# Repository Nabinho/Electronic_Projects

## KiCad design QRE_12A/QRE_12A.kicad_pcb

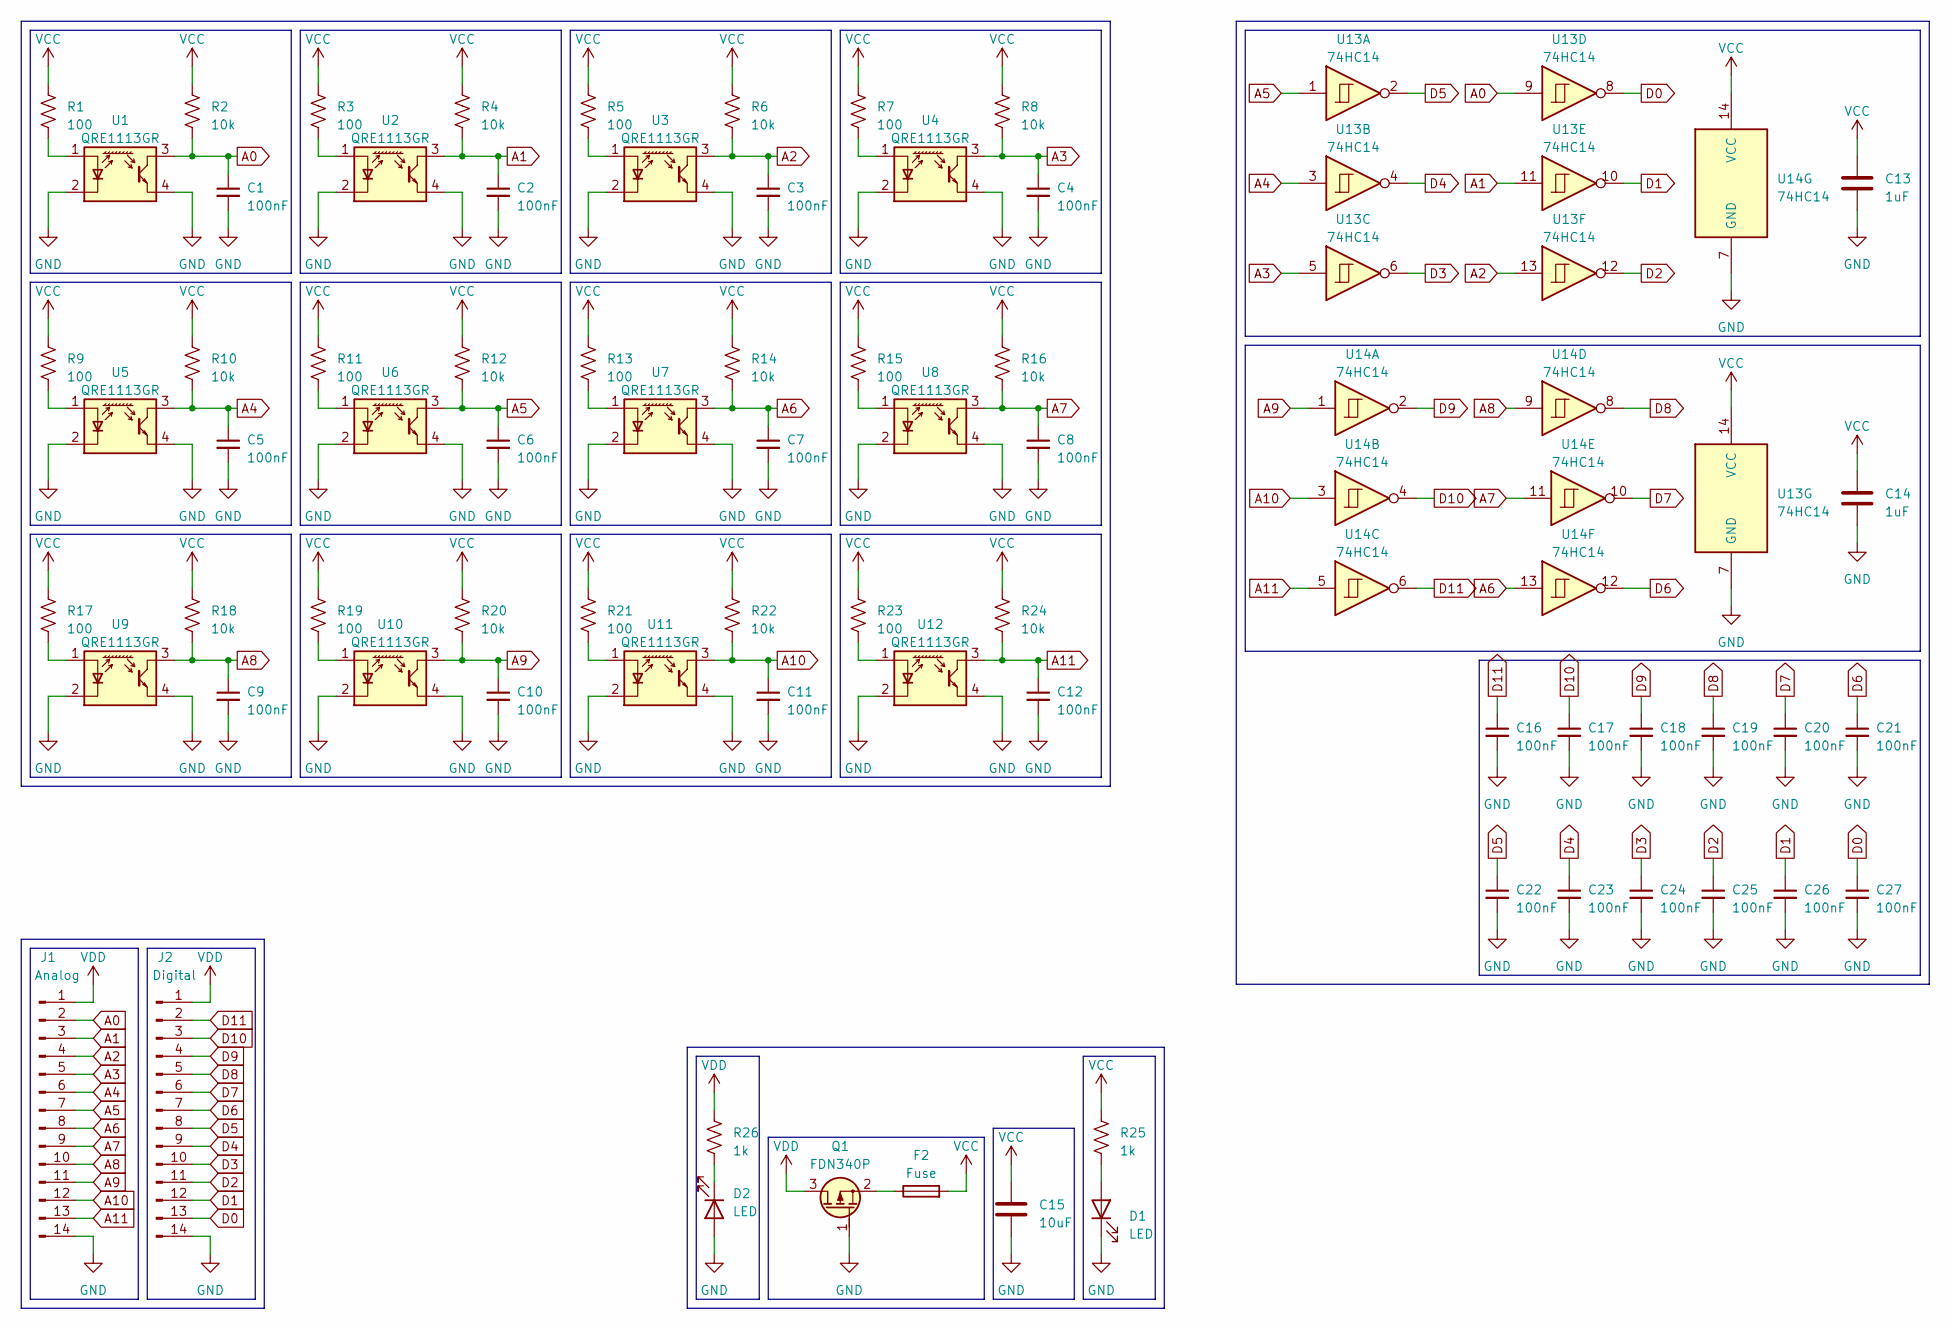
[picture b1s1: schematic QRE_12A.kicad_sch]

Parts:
C1, C2, C3, C4, C5, C6, C7, C8, C9, C10, C11, C12, C16, C17, C18, C19, C20, C21, C22, C23, C24, C25, C26, C27: 100nF; C_0603_1608Metric
C13, C14: 1uF; C_0603_1608Metric
C15: 10uF; C_0805_2012Metric
D1, D2: LED; LED_0603_1608Metric
F2: Fuse; Fuse_0805_2012Metric
J1: Analog; PinSocket_1x14_P2.54mm_Vertical
J2: Digital; PinSocket_1x14_P2.54mm_Vertical
Q1: FDN340P; SOT-23
R1, R3, R5, R7, R9, R11, R13, R15, R17, R19, R21, R23: 100; R_0603_1608Metric
R2, R4, R6, R8, R10, R12, R14, R16, R18, R20, R22, R24: 10k; R_0603_1608Metric
R25, R26: 1k; R_0603_1608Metric
U1, U2, U3, U4, U5, U6, U7, U8, U9, U10, U11, U12: QRE1113GR; OnSemi_CASE100CY
U13, U14: 74HC14; SOIC-14_3.9x8.7mm_P1.27mm

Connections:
A0: C1.1, J1.2, R2.2, U1.3, U13.9
A1: C2.1, J1.3, R4.2, U2.3, U13.11
A2: C3.1, J1.4, R6.2, U3.3, U13.13
A3: C4.1, J1.5, R8.2, U4.3, U13.5
A4: C5.1, J1.6, R10.2, U5.3, U13.3
A5: C6.1, J1.7, R12.2, U6.3, U13.1
A6: C7.1, J1.8, R14.2, U7.3, U14.13
A7: C8.1, J1.9, R16.2, U8.3, U14.11
A8: C9.1, J1.10, R18.2, U9.3, U14.9
A9: C10.1, J1.11, R20.2, U10.3, U14.1
A10: C11.1, J1.12, R22.2, U11.3, U14.3
A11: C12.1, J1.13, R24.2, U12.3, U14.5
D0: C27.1, J2.13, U13.8
D1: C26.1, J2.12, U13.10
D2: C25.1, J2.11, U13.12
D3: C24.1, J2.10, U13.6
D4: C23.1, J2.9, U13.4
D5: C22.1, J2.8, U13.2
D6: C21.1, J2.7, U14.12
D7: C20.1, J2.6, U14.10
D8: C19.1, J2.5, U14.8
D9: C18.1, J2.4, U14.2
D10: C17.1, J2.3, U14.4
D11: C16.1, J2.2, U14.6
GND: C1.2, C2.2, C3.2, C4.2, C5.2, C6.2, C7.2, C8.2, C9.2, C10.2, C11.2, C12.2, C13.2, C14.2, C15.2, C16.2, C17.2, C18.2, C19.2, C20.2, C21.2, C22.2, C23.2, C24.2, C25.2, C26.2, C27.2, D1.1 (K), D2.2 (A), J1.14, J2.14, Q1.1 (G), U1.2 (K), U1.4, U2.2 (K), U2.4, U3.2 (K), U3.4, U4.2 (K), U4.4, U5.2 (K), U5.4, U6.2 (K), U6.4, U7.2 (K), U7.4, U8.2 (K), U8.4, U9.2 (K), U9.4, U10.2 (K), U10.4, U11.2 (K), U11.4, U12.2 (K), U12.4, U13.7 (GND), U14.7 (GND)
unnamed: D1.2 (A), R25.2
unnamed: D2.1 (K), R26.2
unnamed: F2.1, Q1.2 (S)
unnamed: R1.2, U1.1 (A)
unnamed: R3.2, U2.1 (A)
unnamed: R5.2, U3.1 (A)
unnamed: R7.2, U4.1 (A)
unnamed: R9.2, U5.1 (A)
unnamed: R11.2, U6.1 (A)
unnamed: R13.2, U7.1 (A)
unnamed: R15.2, U8.1 (A)
unnamed: R17.2, U9.1 (A)
unnamed: R19.2, U10.1 (A)
unnamed: R21.2, U11.1 (A)
unnamed: R23.2, U12.1 (A)
VCC: C13.1, C14.1, C15.1, F2.2, R1.1, R2.1, R3.1, R4.1, R5.1, R6.1, R7.1, R8.1, R9.1, R10.1, R11.1, R12.1, R13.1, R14.1, R15.1, R16.1, R17.1, R18.1, R19.1, R20.1, R21.1, R22.1, R23.1, R24.1, R25.1, U13.14 (VCC), U14.14 (VCC)
VDD: J1.1, J2.1, Q1.3 (D), R26.1

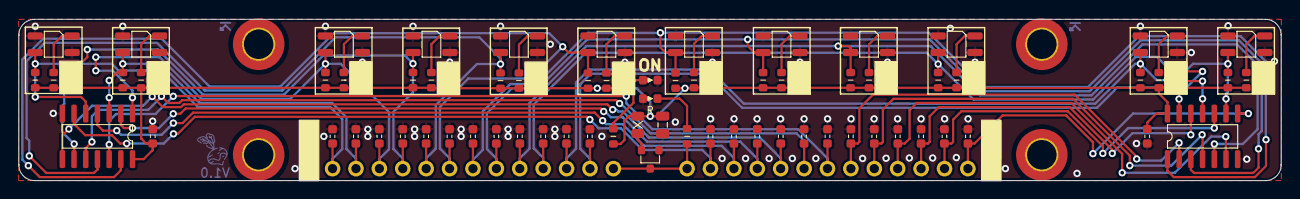
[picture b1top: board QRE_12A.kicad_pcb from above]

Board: 2 copper layers, 137.0 x 17.5 mm, 73 parts (0 on the bottom side), 42 nets.

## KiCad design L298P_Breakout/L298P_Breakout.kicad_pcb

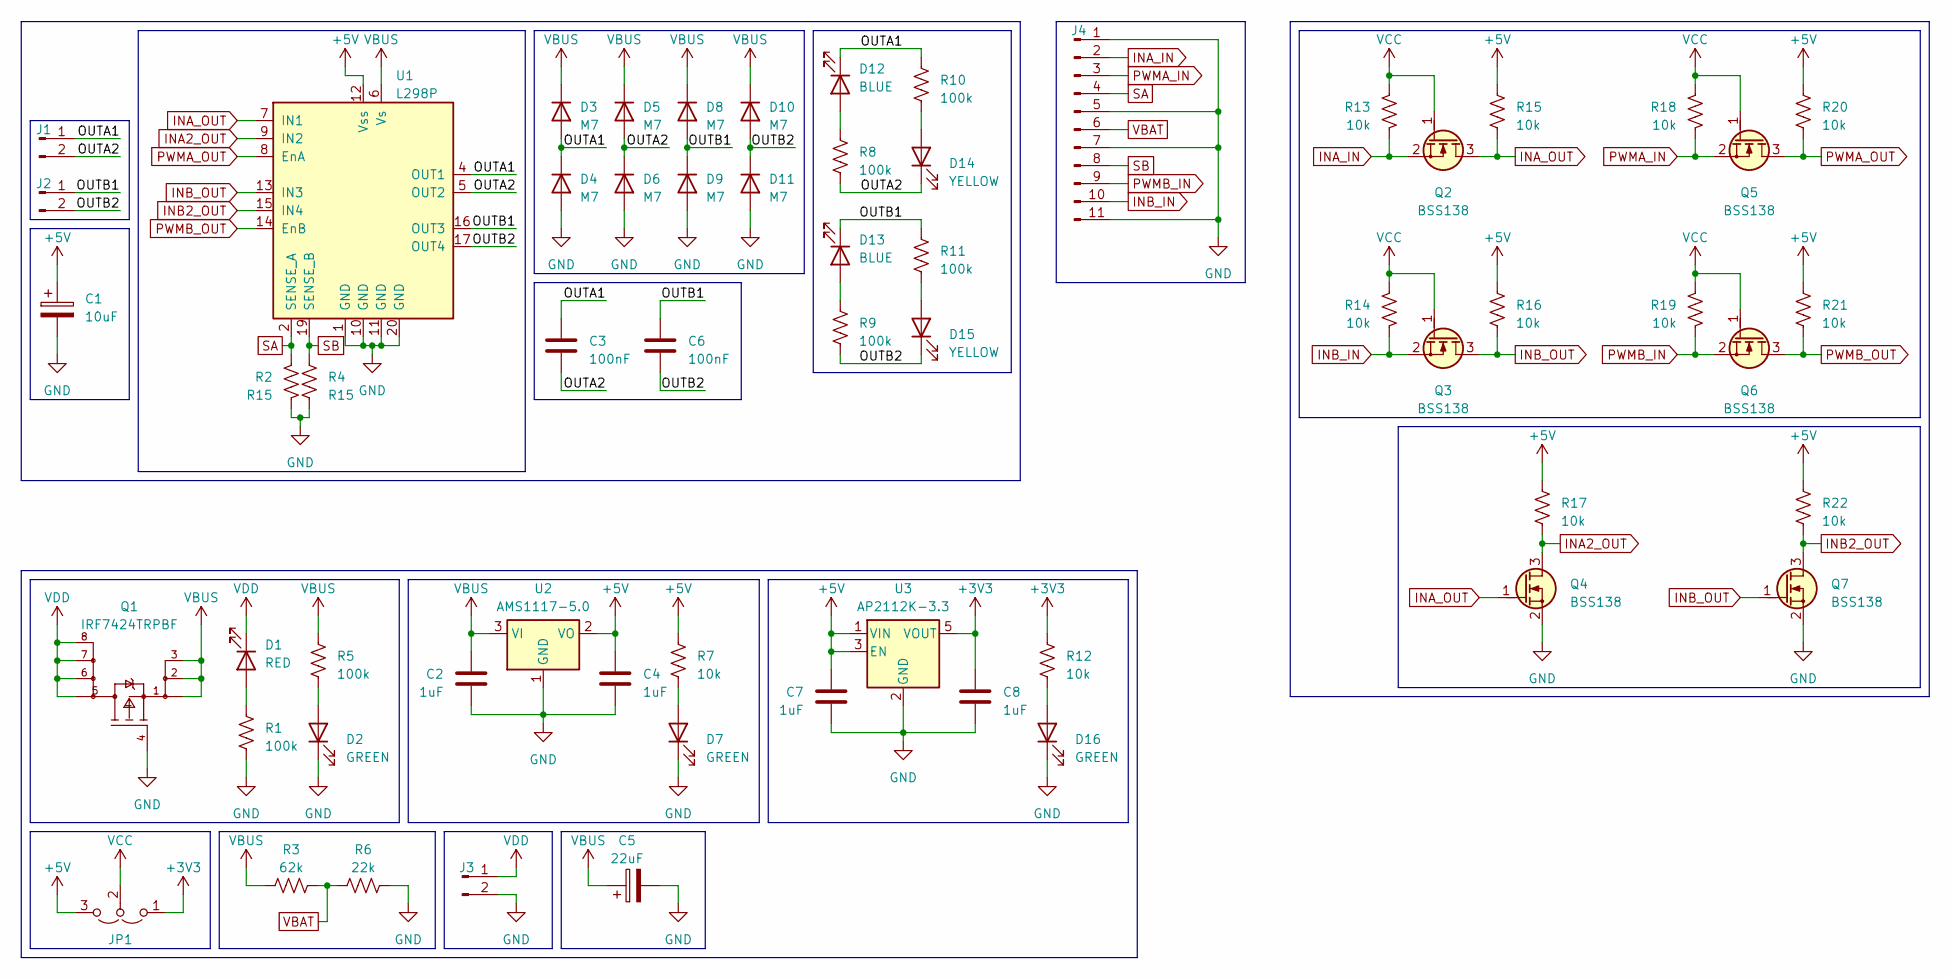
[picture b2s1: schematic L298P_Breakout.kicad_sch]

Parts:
C1: 10uF; CP_EIA-3528-21_Kemet-B
C2, C4, C7, C8: 1uF; C_0603_1608Metric
C3, C6: 100nF; C_0805_2012Metric
C5: 22uF; CP_EIA-3528-21_Kemet-B
D1: RED; LED_0805_2012Metric
D2, D7, D16: GREEN; LED_0805_2012Metric
D3, D4, D5, D6, D8, D9, D10, D11: M7; D_SMA
D12, D13: BLUE; LED_0805_2012Metric
D14, D15: YELLOW; LED_0805_2012Metric
J1, J2, J3: Conn_01x02_Pin; Degson_3.5_2_15EDGRC
J4: Conn_01x11_Pin; PinHeader_1x11_P2.54mm_Vertical
JP1: Jumper_3_Open; SolderJumper-3_P1.3mm_Open_RoundedPad1.0x1.5mm
Q1: IRF7424TRPBF; Infineon-PG-DSO-8-11_2006-902-MFG; mouser part number 942-IRF7424TRPBF; digikey description MOSFET P-CH 30V 11A 8-SOIC
Q2, Q3, Q4, Q5, Q6, Q7: BSS138; SOT-23
R1, R5, R8, R9, R10, R11: 100k; R_0805_2012Metric
R2, R4: R15; R_1206_3216Metric
R3: 62k; R_0805_2012Metric
R6: 22k; R_0805_2012Metric
R7, R12: 10k; R_0805_2012Metric
R13, R14, R15, R16, R17, R18, R19, R20, R21, R22: 10k; R_0603_1608Metric
U1: L298P; STMicroelectronics-L298P-0
U2: AMS1117-5.0; SOT-223-3_TabPin2
U3: AP2112K-3.3; SOT-23-5

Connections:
+3V3: C8.1, JP1.1 (A), R12.1, U3.5 (VOUT)
+5V: C1.1, C4.1, C7.1, JP1.3 (B), R7.1, R15.1, R16.1, R17.1, R20.1, R21.1, R22.1, U1.12 (Vss), U2.2 (VO), U3.1 (VIN), U3.3 (EN)
/OUTA1: C3.1, D3.2 (A), D4.1 (K), D12.1 (K), J1.1, R10.1, U1.4 (OUT1)
/OUTA2: C3.2, D5.2 (A), D6.1 (K), D14.1 (K), J1.2, R8.2, U1.5 (OUT2)
/OUTB1: C6.1, D8.2 (A), D9.1 (K), D13.1 (K), J2.1, R11.1, U1.16 (OUT3)
/OUTB2: C6.2, D10.2 (A), D11.1 (K), D15.1 (K), J2.2, R9.2, U1.17 (OUT4)
GND: C1.2, C2.2, C4.2, C5.2, C7.2, C8.2, D2.1 (K), D4.2 (A), D6.2 (A), D7.1 (K), D9.2 (A), D11.2 (A), D16.1 (K), J3.2, J4.1, J4.5, J4.7, J4.11, Q1.4 (G), Q4.2 (S), Q7.2 (S), R1.2, R2.2, R4.2, R6.2, U1.1 (GND), U1.10 (GND), U1.11 (GND), U1.20 (GND), U1.21, U2.1 (GND), U3.2 (GND)
INA2_OUT: Q4.3 (D), R17.2, U1.9 (IN2)
INA_IN: J4.2, Q2.2 (S), R13.2
INA_OUT: Q2.3 (D), Q4.1 (G), R15.2, U1.7 (IN1)
INB2_OUT: Q7.3 (D), R22.2, U1.15 (IN4)
INB_IN: J4.10, Q3.2 (S), R14.2
INB_OUT: Q3.3 (D), Q7.1 (G), R16.2, U1.13 (IN3)
unnamed: D1.2 (A), R1.1
unnamed: D2.2 (A), R5.2
unnamed: D7.2 (A), R7.2
unnamed: D12.2 (A), R8.1
unnamed: D13.2 (A), R9.1
unnamed: D14.2 (A), R10.2
unnamed: D15.2 (A), R11.2
unnamed: D16.2 (A), R12.2
PWMA_IN: J4.3, Q5.2 (S), R18.2
PWMA_OUT: Q5.3 (D), R20.2, U1.8 (EnA)
PWMB_IN: J4.9, Q6.2 (S), R19.2
PWMB_OUT: Q6.3 (D), R21.2, U1.14 (EnB)
SA: J4.4, R2.1, U1.2 (SENSE_A)
SB: J4.8, R4.1, U1.19 (SENSE_B)
VBAT: J4.6, R3.2, R6.1
VBUS: C2.1, C5.1, D3.1 (K), D5.1 (K), D8.1 (K), D10.1 (K), Q1.1 (S), Q1.2 (S), Q1.3 (S), R3.1, R5.1, U1.6 (Vs), U2.3 (VI)
VCC: JP1.2 (C), Q2.1 (G), Q3.1 (G), Q5.1 (G), Q6.1 (G), R13.1, R14.1, R18.1, R19.1
VDD: D1.1 (K), J3.1, Q1.5 (D), Q1.6 (D), Q1.7 (D), Q1.8 (D)

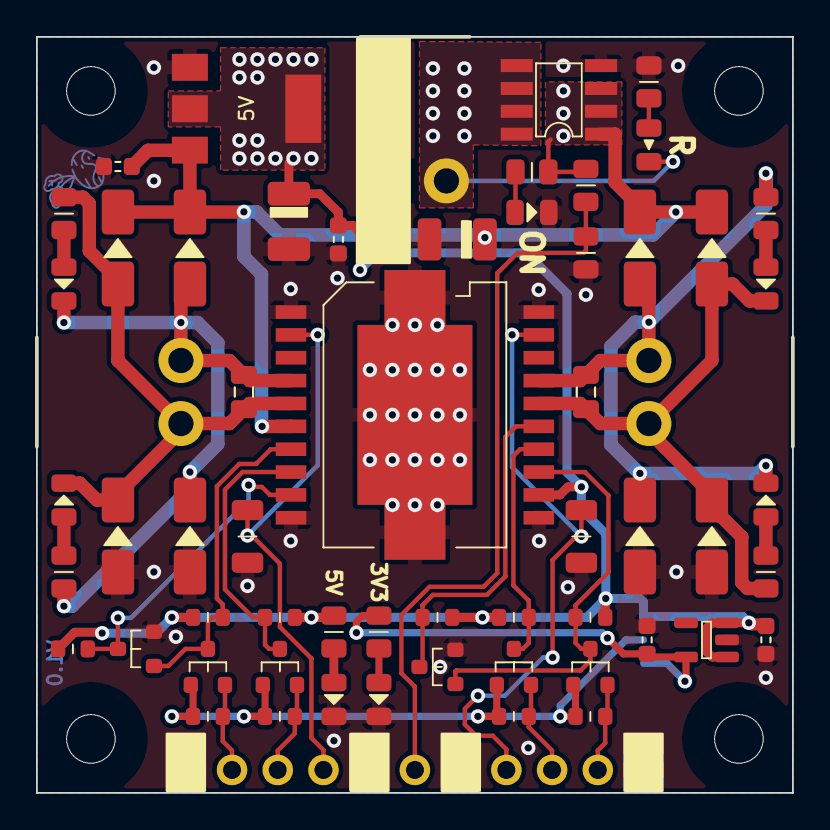
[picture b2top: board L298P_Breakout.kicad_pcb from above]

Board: 2 copper layers, 42.0 x 42.0 mm, 61 parts (1 on the bottom side), 31 nets.

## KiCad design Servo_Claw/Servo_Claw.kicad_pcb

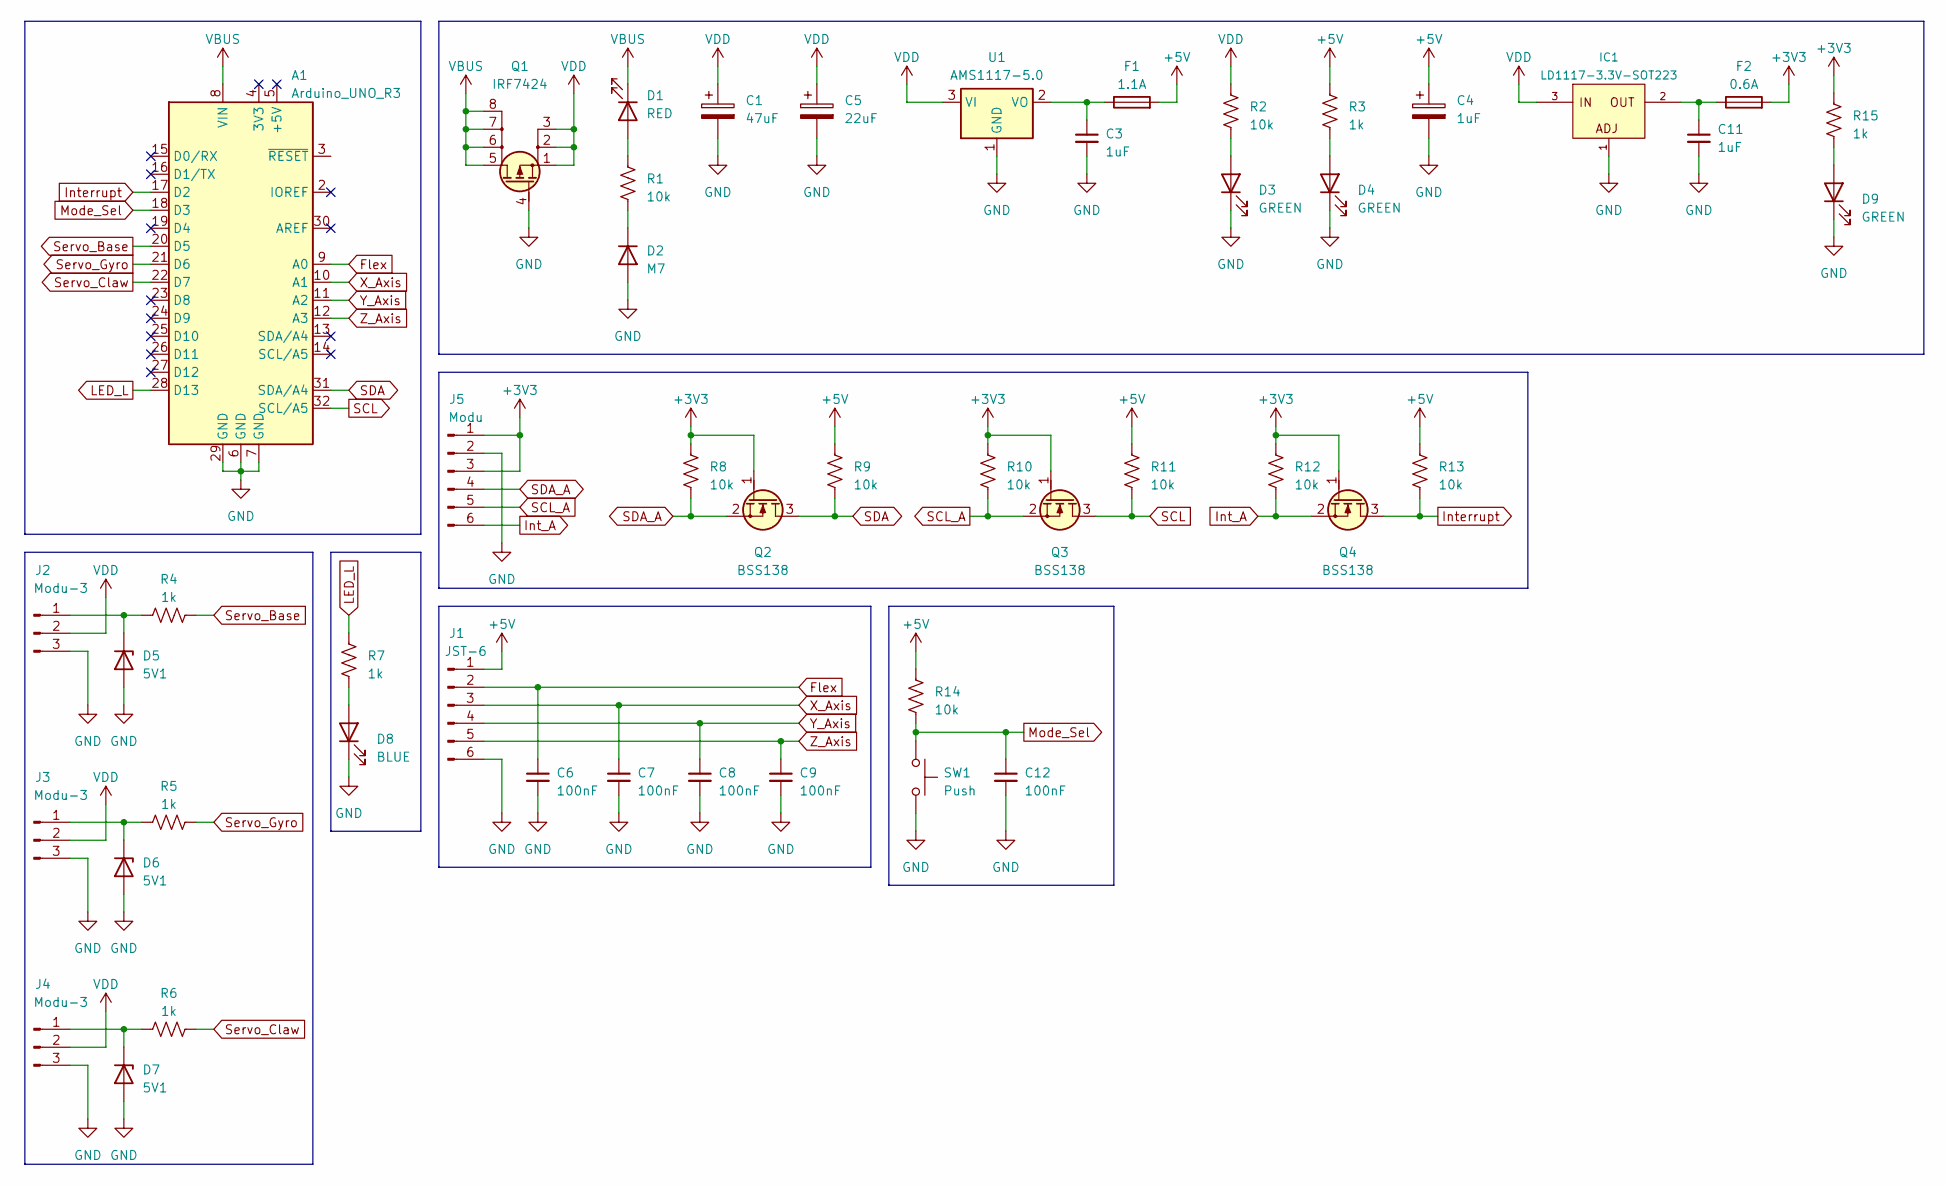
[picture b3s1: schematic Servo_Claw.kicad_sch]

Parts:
A1: Arduino_UNO_R3; Arduino_UNO_R3_WithMountingHoles
C1: 47uF; CP_Elec_6.3x4.9
C3, C11: 1uF; C_0805_2012Metric
C4: 1uF; CP_EIA-3528-21_Kemet-B
C5: 22uF; CP_EIA-7343-31_Kemet-D
C6, C7, C8, C9, C12: 100nF; C_0805_2012Metric
D1: RED; LED_0805_2012Metric
D2: M7; D_SMA
D3, D4, D9: GREEN; LED_0805_2012Metric
D5, D6, D7: 5V1; D_MiniMELF
D8: BLUE; LED_0805_2012Metric
F1: 1.1A; Fuse_1812_4532Metric
F2: 0.6A; Fuse_0805_2012Metric
IC1: LD1117-3.3V-SOT223; SOT-223-3_TabPin2; Part Number LD1117S33CTR
J1: JST-6; JST_PH_B6B-PH-K_1x06_P2.00mm_Vertical
J2, J3, J4: Modu-3; PinHeader_1x03_P2.54mm_Vertical
J5: Modu; PinSocket_1x06_P2.54mm_Vertical
Q1: IRF7424; SO-8_3.9x4.9mm_P1.27mm
Q2, Q3, Q4: BSS138; SOT-23
R1, R2, R8, R9, R10, R11, R12, R13, R14: 10k; R_0805_2012Metric
R3, R4, R5, R6, R7, R15: 1k; R_0805_2012Metric
SW1: Push; SW_SPST_SKQG_WithStem
U1: AMS1117-5.0; SOT-223-3_TabPin2

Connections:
+3V3: F2.2, J5.1, J5.3, Q2.1 (G), Q3.1 (G), Q4.1 (G), R8.1, R10.1, R12.1, R15.1
+5V: C4.1, F1.2, J1.1, R3.1, R9.1, R11.1, R13.1, R14.1
Flex: A1.9 (A0), C6.1, J1.2
GND: A1.6 (GND), A1.7 (GND), A1.29 (GND), C1.2, C3.2, C4.2, C5.2, C6.2, C7.2, C8.2, C9.2, C11.2, C12.2, D2.2 (A), D3.1 (K), D4.1 (K), D5.2 (A), D6.2 (A), D7.2 (A), D8.1 (K), D9.1 (K), IC1.1 (ADJ), J1.6, J2.3, J3.3, J4.3, J5.2, Q1.4 (G), SW1.2, U1.1 (GND)
Int_A: J5.6, Q4.2 (S), R12.2
Interrupt: A1.17 (D2), Q4.3 (D), R13.2
LED_L: A1.28 (D13), R7.1
Mode_Sel: A1.18 (D3), C12.1, R14.2, SW1.1
unnamed: D1.2 (A), R1.1
unnamed: D2.1 (K), R1.2
unnamed: D3.2 (A), R2.2
unnamed: D4.2 (A), R3.2
unnamed: D5.1 (K), J2.1, R4.1
unnamed: D6.1 (K), J3.1, R5.1
unnamed: D7.1 (K), J4.1, R6.1
unnamed: D8.2 (A), R7.2
unnamed: D9.2 (A), R15.2
unnamed: C11.1, F2.1, IC1.2 (OUT)
unnamed: C3.1, F1.1, U1.2 (VO)
SCL: A1.32 (SCL/A5), Q3.3 (D), R11.2
SCL_A: J5.5, Q3.2 (S), R10.2
SDA: A1.31 (SDA/A4), Q2.3 (D), R9.2
SDA_A: J5.4, Q2.2 (S), R8.2
Servo_Base: A1.20 (D5), R4.2
Servo_Claw: A1.22 (D7), R6.2
Servo_Gyro: A1.21 (D6), R5.2
VBUS: A1.8 (VIN), D1.1 (K), Q1.5 (D), Q1.6 (D), Q1.7 (D), Q1.8 (D)
VDD: C1.1, C5.1, IC1.3 (IN), J2.2, J3.2, J4.2, Q1.1 (S), Q1.2 (S), Q1.3 (S), R2.1, U1.3 (VI)
X_Axis: A1.10 (A1), C7.1, J1.3
Y_Axis: A1.11 (A2), C8.1, J1.4
Z_Axis: A1.12 (A3), C9.1, J1.5

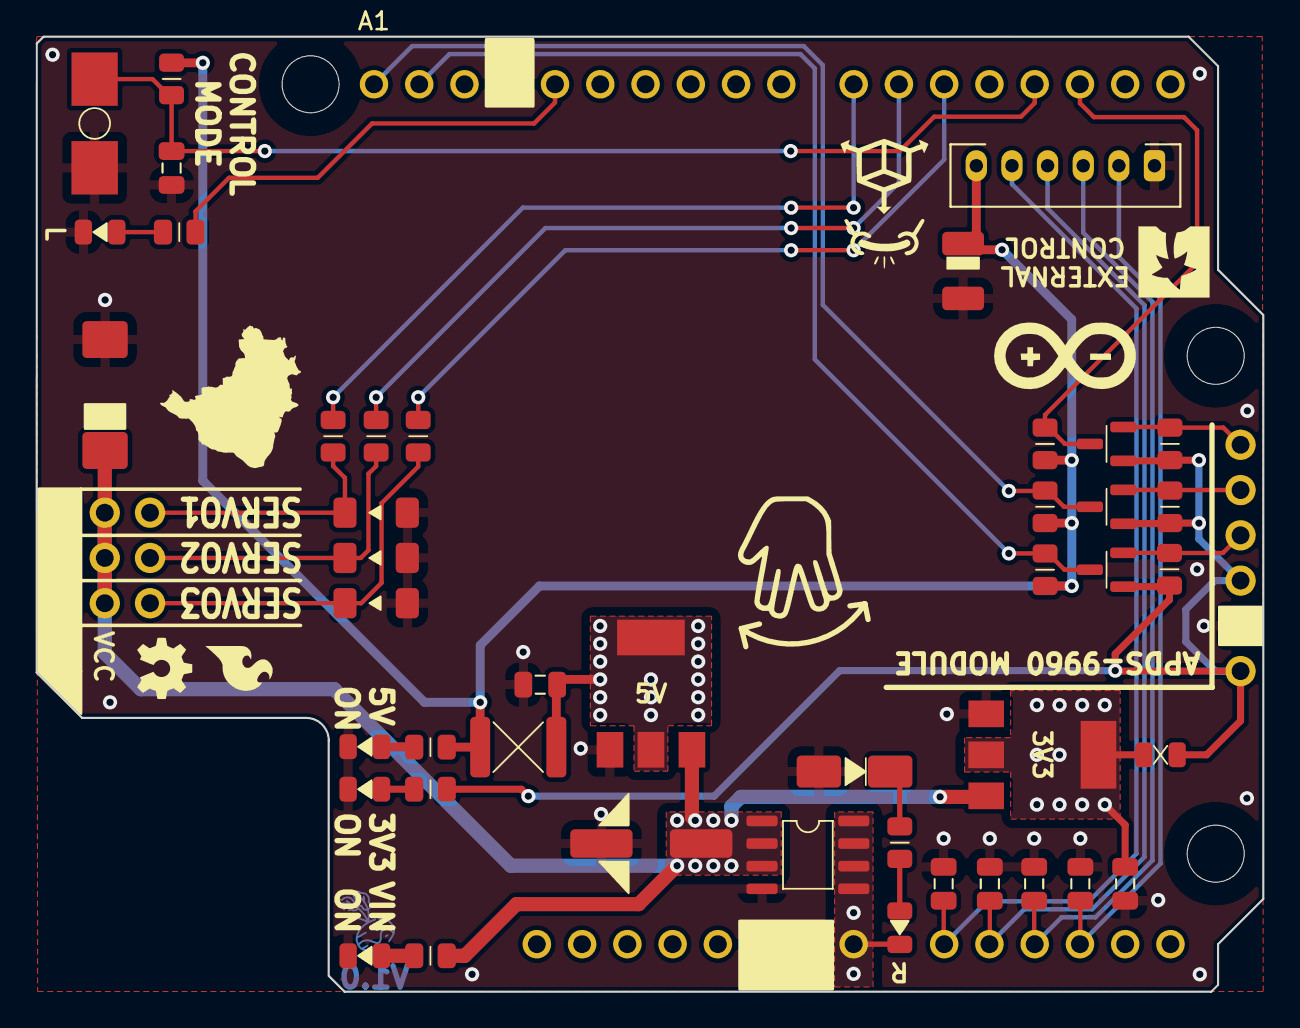
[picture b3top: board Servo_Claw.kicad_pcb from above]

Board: 2 copper layers, 68.8 x 53.6 mm, 49 parts (0 on the bottom side), 31 nets.

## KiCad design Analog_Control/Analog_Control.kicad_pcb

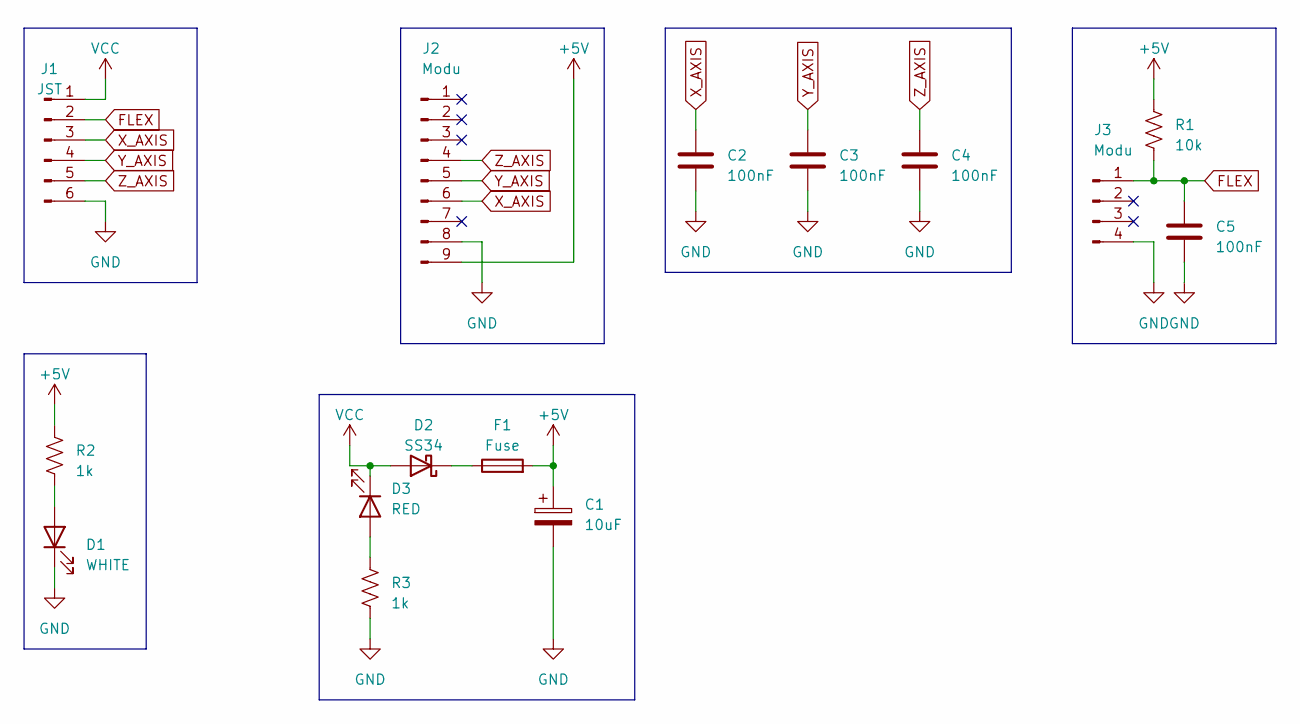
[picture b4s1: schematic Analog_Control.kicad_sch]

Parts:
C1: 10uF; CP_EIA-3528-21_Kemet-B
C2, C3, C4, C5: 100nF; C_0805_2012Metric
D1: WHITE; LED_0805_2012Metric
D2: SS34; D_SMA
D3: RED; LED_0805_2012Metric
F1: Fuse; Fuse_1210_3225Metric
J1: JST; JST_PH_S6B-PH-K_1x06_P2.00mm_Horizontal
J2: Modu; PinSocket_1x09_P2.54mm_Vertical
J3: Modu; PinSocket_1x04_P2.54mm_Vertical_SMD_Pin1Left
R1: 10k; R_0805_2012Metric
R2, R3: 1k; R_0805_2012Metric

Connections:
+5V: C1.1, F1.2, J2.9, R1.1, R2.1
FLEX: C5.1, J1.2, J3.1, R1.2
GND: C1.2, C2.2, C3.2, C4.2, C5.2, D1.1 (K), J1.6, J2.8, J3.4, R3.2
unnamed: D1.2 (A), R2.2
unnamed: D2.1 (K), F1.1
unnamed: D3.2 (A), R3.1
VCC: D2.2 (A), D3.1 (K), J1.1
X_AXIS: C2.1, J1.3, J2.6
Y_AXIS: C3.1, J1.4, J2.5
Z_AXIS: C4.1, J1.5, J2.4

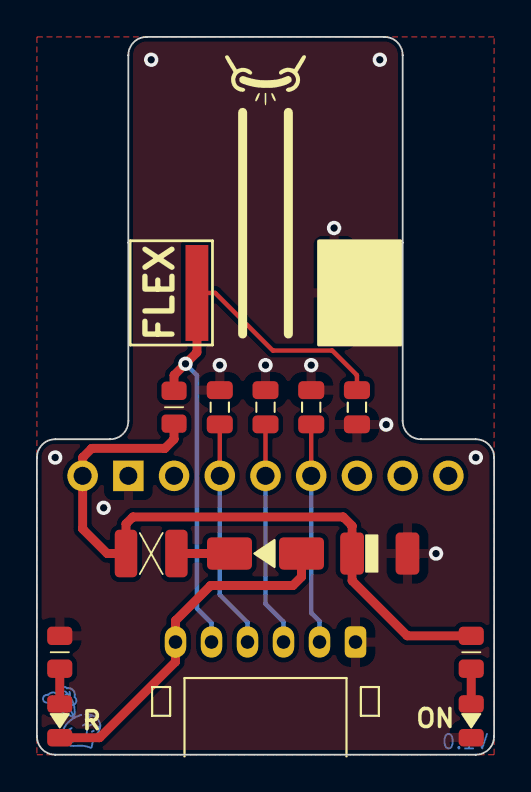
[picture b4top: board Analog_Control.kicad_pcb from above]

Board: 2 copper layers, 25.4 x 39.9 mm, 15 parts (0 on the bottom side), 10 nets.

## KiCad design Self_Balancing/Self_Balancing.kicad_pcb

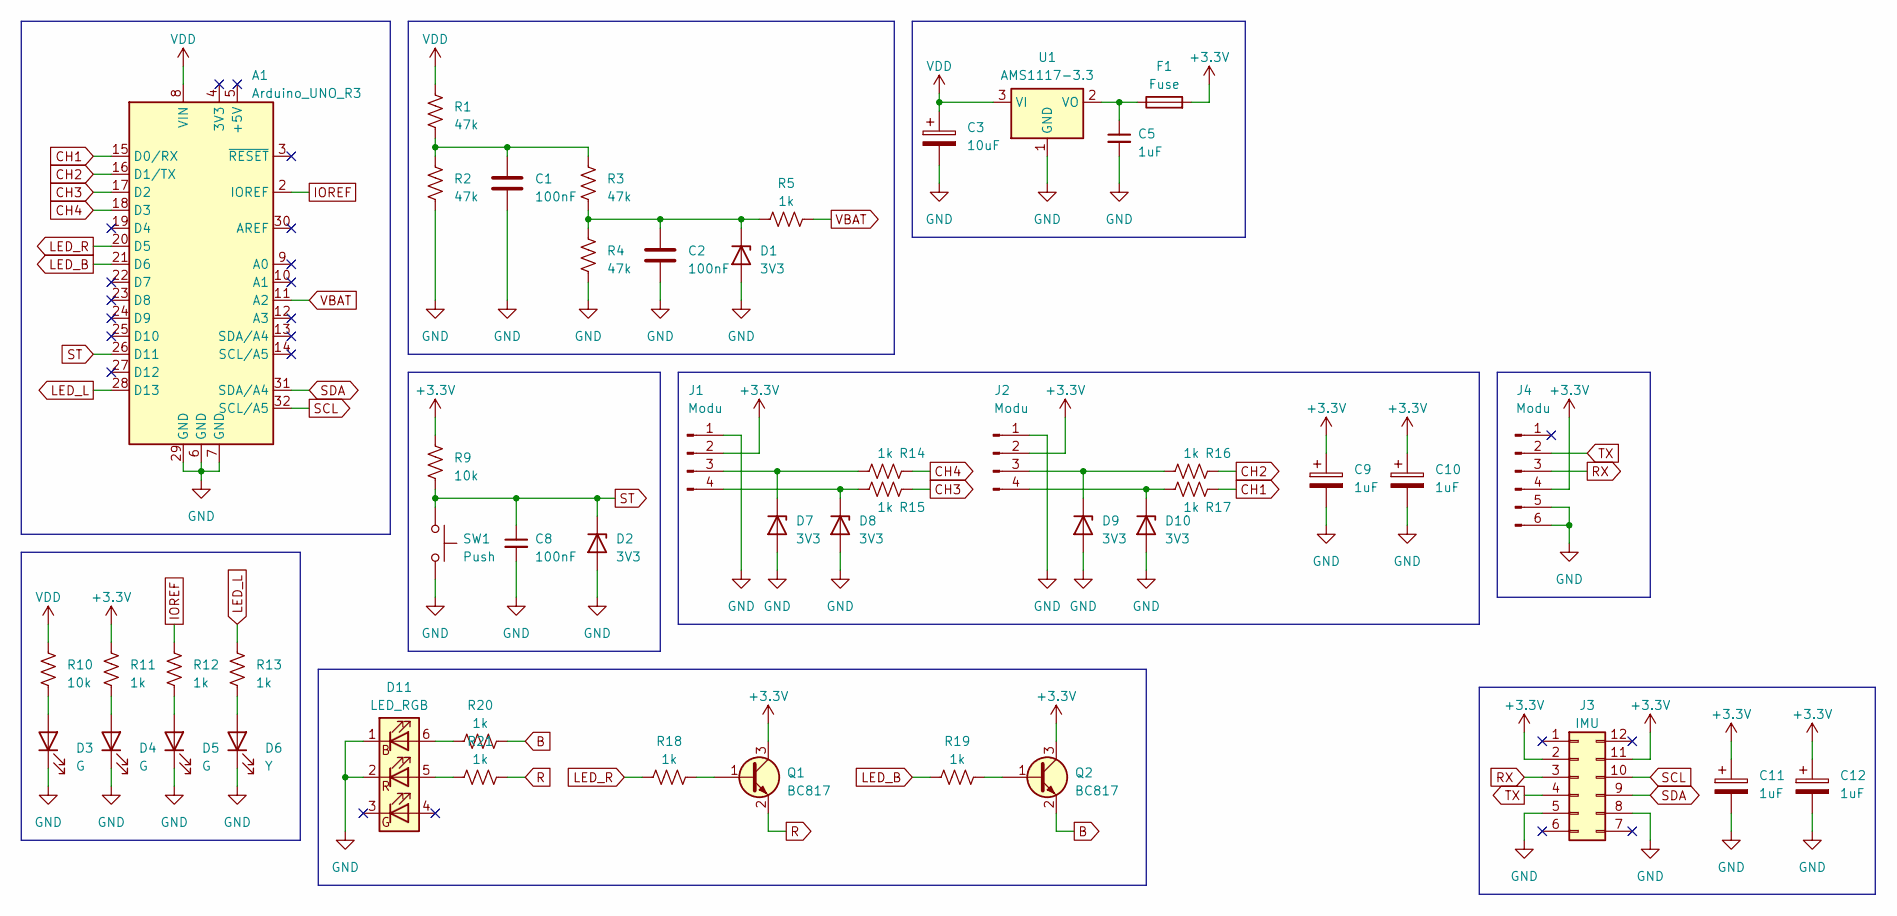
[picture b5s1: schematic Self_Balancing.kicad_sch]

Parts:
A1: Arduino_UNO_R3
C1, C2, C8: 100nF; C_0805_2012Metric
C3: 10uF; CP_Elec_4x3.9
C5: 1uF; C_0805_2012Metric
C9, C10: 1uF; CP_EIA-3216-18_Kemet-A
C11, C12: 1uF; CP_EIA-3528-21_Kemet-B
D1, D2, D7, D8, D9, D10: 3V3; D_MiniMELF
D3, D4, D5: G; LED_0805_2012Metric
D6: Y; LED_0805_2012Metric
D11: LED_RGB; LED_RGB_5050-6
F1: Fuse; Fuseholder_Littelfuse_Nano2_157x
J1, J2: Modu; PinHeader_1x04_P2.54mm_Vertical
J3: IMU
J4: Modu; PinHeader_1x06_P2.54mm_Horizontal
Q1, Q2: BC817; SOT-23
R1, R2, R3, R4: 47k; R_Axial_DIN0207_L6.3mm_D2.5mm_P7.62mm_Horizontal
R5, R11, R12, R13, R14, R15, R16, R17, R18, R19, R20, R21: 1k; R_0805_2012Metric
R9, R10: 10k; R_0805_2012Metric
SW1: Push; SW_PUSH-12mm
U1: AMS1117-3.3; SOT-223-3_TabPin2

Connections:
+3V3: C9.1, C10.1, C11.1, C12.1, F1.2, J1.2, J2.2, J3.2, J3.11, J4.4, Q1.3 (C), Q2.3 (C), R9.1, R11.1
B: Q2.2 (E), R20.2
CH1: A1.15 (D0/RX), R17.2
CH2: A1.16 (D1/TX), R16.2
CH3: A1.17 (D2), R15.2
CH4: A1.18 (D3), R14.2
GND: A1.6 (GND), A1.7 (GND), A1.29 (GND), C1.2, C2.2, C3.2, C5.2, C8.2, C9.2, C10.2, C11.2, C12.2, D1.2 (A), D2.2 (A), D3.1 (K), D4.1 (K), D5.1 (K), D6.1 (K), D7.2 (A), D8.2 (A), D9.2 (A), D10.2 (A), D11.1 (RK), D11.2 (GK), J1.1, J2.1, J3.5, J3.8, J4.5, J4.6, R2.2, R4.2, SW1.2, U1.1 (GND)
IOREF: A1.2 (IOREF), R12.1
LED_B: A1.21 (D6), R19.1
LED_L: A1.28 (D13), R13.1
LED_R: A1.20 (D5), R18.1
unnamed: C1.1, R1.2, R2.1, R3.1
unnamed: C2.1, D1.1 (K), R3.2, R4.1, R5.1
unnamed: D3.2 (A), R10.2
unnamed: D4.2 (A), R11.2
unnamed: D5.2 (A), R12.2
unnamed: D6.2 (A), R13.2
unnamed: D7.1 (K), J1.3, R14.1
unnamed: D8.1 (K), J1.4, R15.1
unnamed: D9.1 (K), J2.3, R16.1
unnamed: D10.1 (K), J2.4, R17.1
unnamed: D11.5 (GA), R21.1
unnamed: D11.6 (RA), R20.1
unnamed: Q1.1 (B), R18.2
unnamed: Q2.1 (B), R19.2
unnamed: C5.1, F1.1, U1.2 (VO)
R: Q1.2 (E), R21.2
RX: J3.3, J4.3
SCL: A1.32 (SCL/A5), J3.10
SDA: A1.31 (SDA/A4), J3.9
ST: A1.26 (D11), C8.1, D2.1 (K), R9.2, SW1.1
TX: J3.4, J4.2
VBAT: A1.11 (A2), R5.2
VDD: A1.8 (VIN), C3.1, R1.1, R10.1, U1.3 (VI)

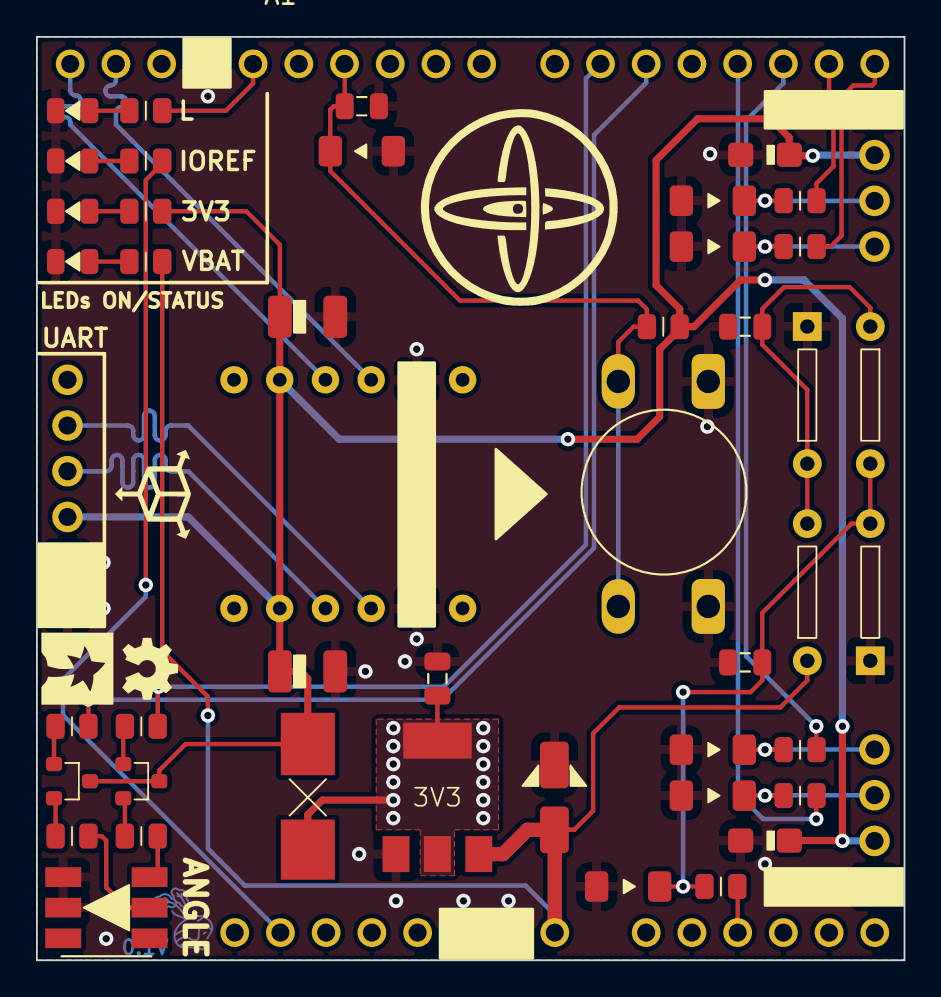
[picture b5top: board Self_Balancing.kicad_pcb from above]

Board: 2 copper layers, 48.2 x 51.3 mm, 48 parts (0 on the bottom side), 34 nets.

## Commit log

2023-05-07 files_upload
2023-09-09 New_Projects
